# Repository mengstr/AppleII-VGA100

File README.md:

# Apple II VGA Card 100mm PCB

This is a smaller (fits within a 100x100 mm PCB) version of the PCB for the Apple II VGA card. The
original project with the firmware and instructions is located at https://github.com/markadev/AppleII-VGA

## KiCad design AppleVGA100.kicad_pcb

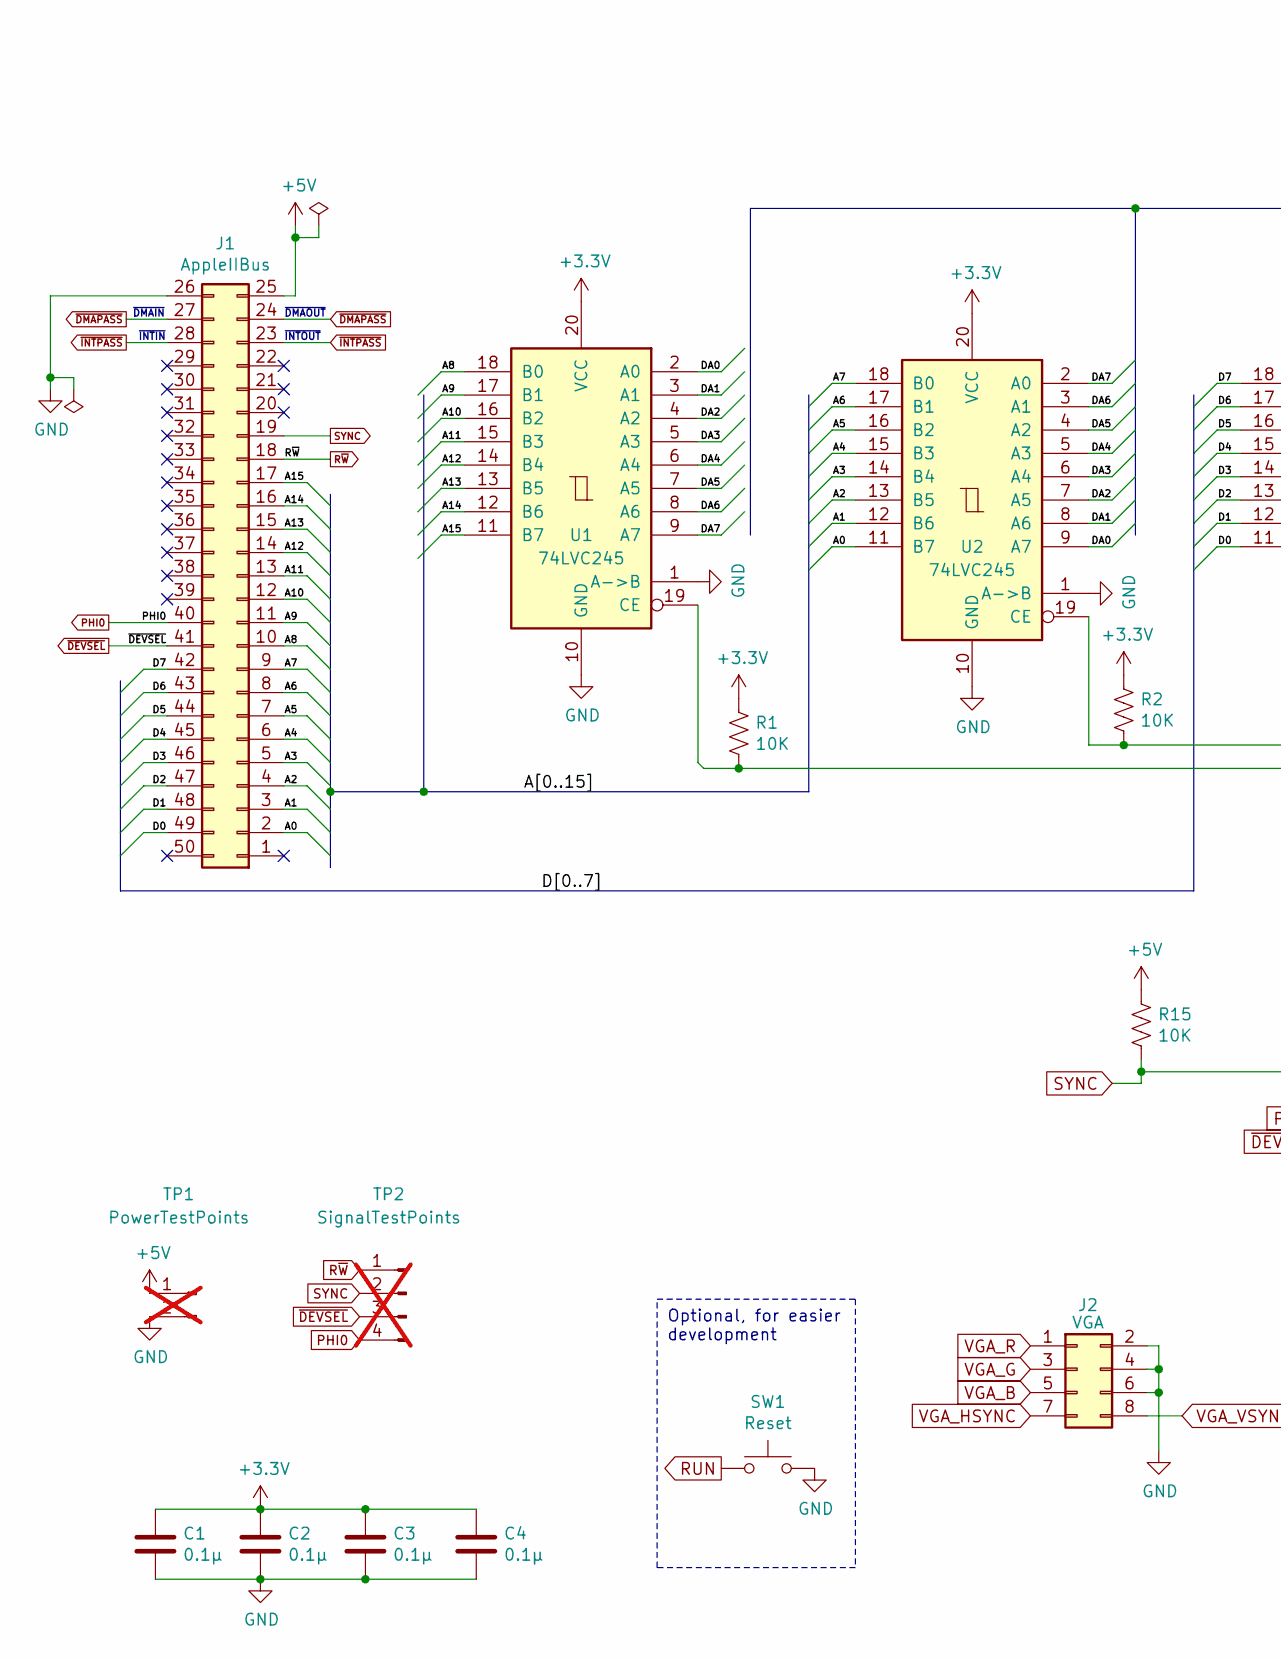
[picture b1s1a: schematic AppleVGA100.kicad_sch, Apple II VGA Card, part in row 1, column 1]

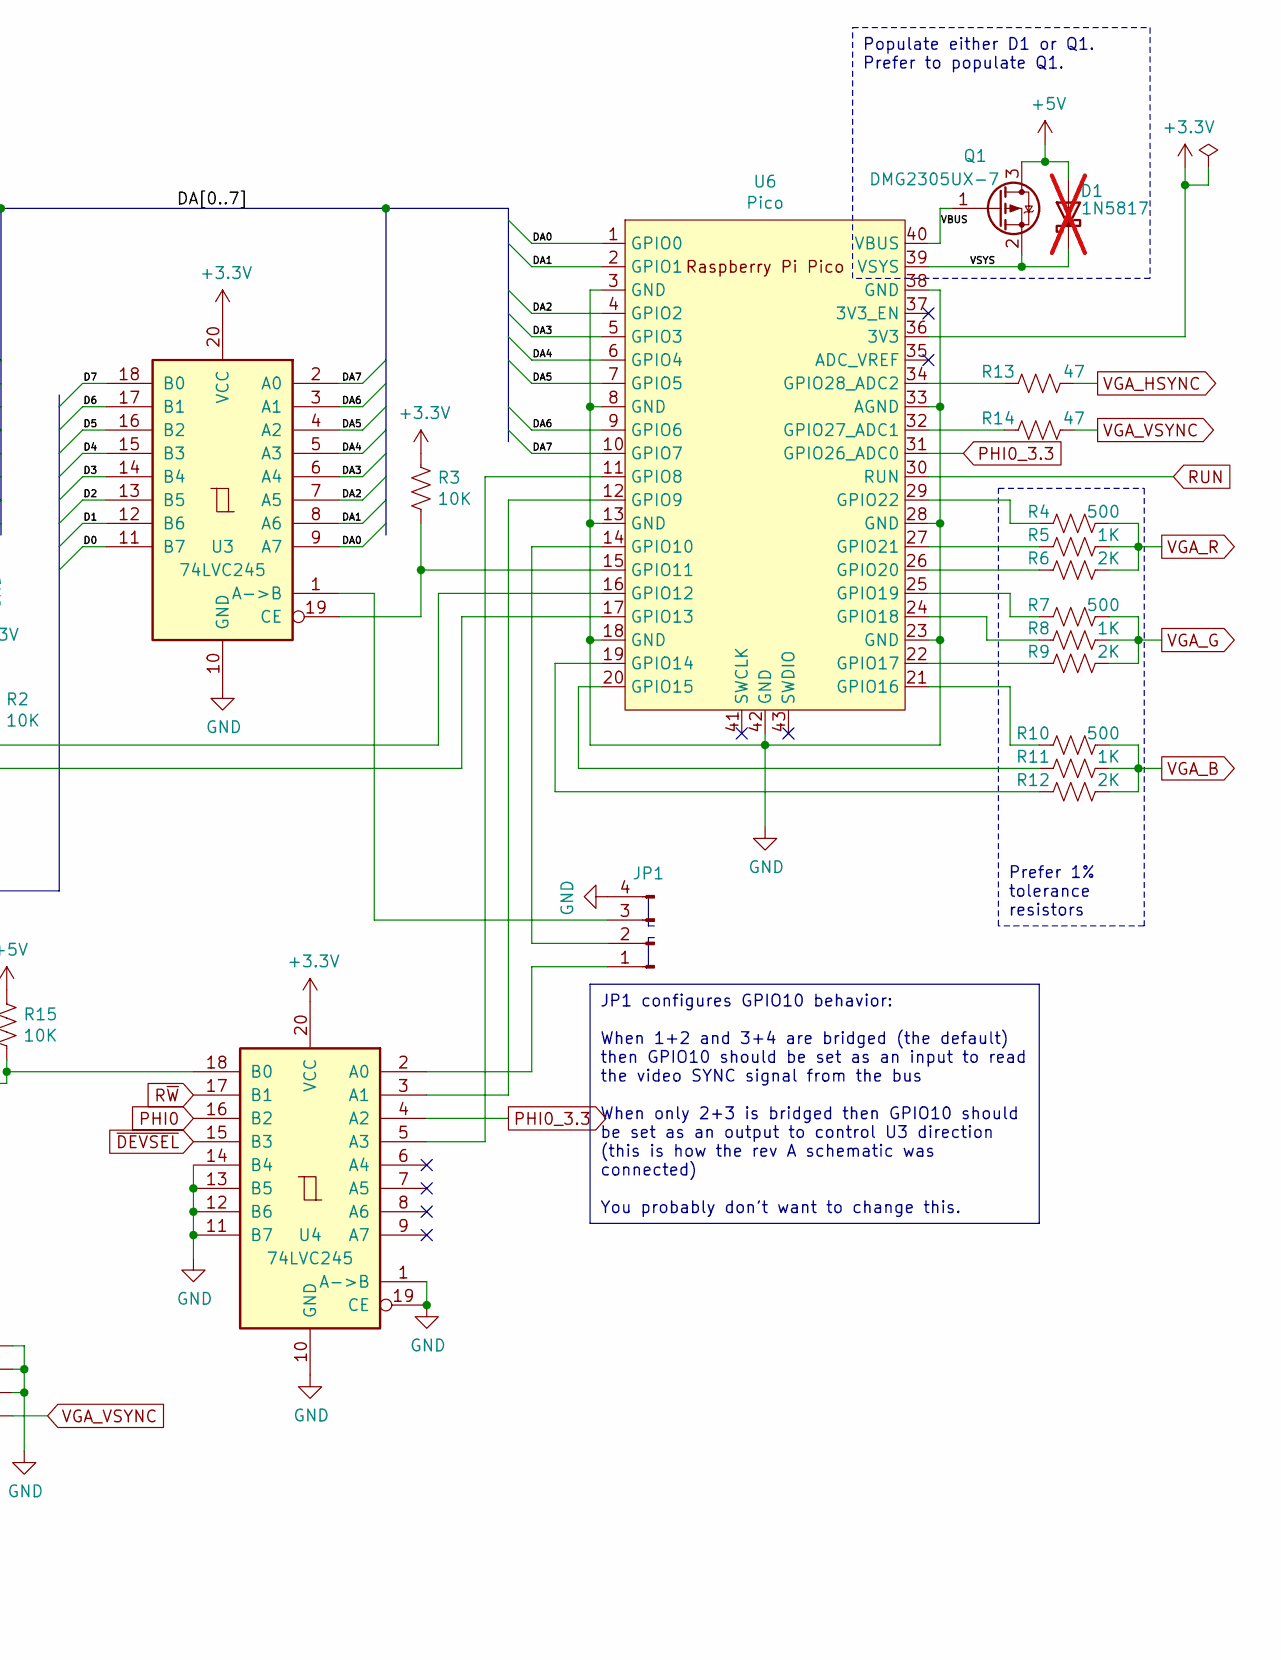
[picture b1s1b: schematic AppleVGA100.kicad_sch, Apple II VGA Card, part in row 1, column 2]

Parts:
C1, C2, C3, C4: 0.1μ; C_Disc_D4.3mm_W1.9mm_P5.00mm; MouserNo 594-A104K15X7RF5TAA
D1: 1N5817; D_DO-41_SOD81_P10.16mm_Horizontal; MouserNo 511-1N5817; not fitted
J1: AppleIIBus; AppleIIBus_Edge
J2: VGA; IDC-Header_2x04_P2.54mm_Vertical; MouserNo 649-75869-232LF
JP1: JumperPads; SolderJumper-4_P1.3mm_Bridged12_34_RoundedPad1.0x1.5mm_Numb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
Q1: DMG2305UX-7; SOT-23; MouserNo 621-DMG2305UX-7
R1, R2, R3, R15: 10K; R_Axial_DIN0207_L6.3mm_D2.5mm_P10.16mm_Thin_Horizontal; MouserNo 603-CFR-25JR-5210K
R4, R7, R10: 500; R_Axial_DIN0207_L6.3mm_D2.5mm_P10.16mm_Thin_Horizontal; MouserNo 603-MFR-25FBF52-499R
R5, R8, R11: 1K; R_Axial_DIN0207_L6.3mm_D2.5mm_P10.16mm_Thin_Horizontal; MouserNo 603-MFR-25FBF52-1K
R6, R9, R12: 2K; R_Axial_DIN0207_L6.3mm_D2.5mm_P10.16mm_Thin_Horizontal; MouserNo 603-MFR-25FBF52-2K
R13, R14: 47; R_Axial_DIN0207_L6.3mm_D2.5mm_P10.16mm_Thin_Horizontal; MouserNo 603-MFR-25FTF52-47R
SW1: Reset; SW_PUSH_6mm_H5mm; MouserNo 506-FSM4JH
TP1: PowerTestPoints; PinHeader_1x02_P2.54mm_Vertical; not fitted
TP2: SignalTestPoints; PinHeader_1x04_P2.54mm_Vertical; not fitted
U1, U2, U3, U4: 74LVC245; DIP-20_W7.62mm_Socket; MouserNo 595-SN74LVC245AN
U6: Pico; RPi_Pico_SMD_TH

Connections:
+3.3V: C1.1, C2.1, C3.1, C4.1, R1.1, R2.1, R3.1, U1.20 (VCC), U2.20 (VCC), U3.20 (VCC), U4.20 (VCC), U6.36 (3V3)
+5V: D1.2 (A), J1.25, Q1.3 (D), R15.1, TP1.1
/A0: J1.2, U2.11 (B7)
/A1: J1.3, U2.12 (B6)
/A2: J1.4, U2.13 (B5)
/A3: J1.5, U2.14 (B4)
/A4: J1.6, U2.15 (B3)
/A5: J1.7, U2.16 (B2)
/A6: J1.8, U2.17 (B1)
/A7: J1.9, U2.18 (B0)
/A8: J1.10, U1.18 (B0)
/A9: J1.11, U1.17 (B1)
/A10: J1.12, U1.16 (B2)
/A11: J1.13, U1.15 (B3)
/A12: J1.14, U1.14 (B4)
/A13: J1.15, U1.13 (B5)
/A14: J1.16, U1.12 (B6)
/A15: J1.17, U1.11 (B7)
/D0: J1.49, U3.11 (B7)
/D1: J1.48, U3.12 (B6)
/D2: J1.47, U3.13 (B5)
/D3: J1.46, U3.14 (B4)
/D4: J1.45, U3.15 (B3)
/D5: J1.44, U3.16 (B2)
/D6: J1.43, U3.17 (B1)
/D7: J1.42, U3.18 (B0)
/DA0: U1.2 (A0), U2.9 (A7), U3.9 (A7), U6.1 (GPIO0)
/DA1: U1.3 (A1), U2.8 (A6), U3.8 (A6), U6.2 (GPIO1)
/DA2: U1.4 (A2), U2.7 (A5), U3.7 (A5), U6.4 (GPIO2)
/DA3: U1.5 (A3), U2.6 (A4), U3.6 (A4), U6.5 (GPIO3)
/DA4: U1.6 (A4), U2.5 (A3), U3.5 (A3), U6.6 (GPIO4)
/DA5: U1.7 (A5), U2.4 (A2), U3.4 (A2), U6.7 (GPIO5)
/DA6: U1.8 (A6), U2.3 (A1), U3.3 (A1), U6.9 (GPIO6)
/DA7: U1.9 (A7), U2.2 (A0), U3.2 (A0), U6.10 (GPIO7)
/VBUS: Q1.1 (G), U6.40 (VBUS)
/VSYS: D1.1 (K), Q1.2 (S), U6.39 (VSYS)
GND: C1.2, C2.2, C3.2, C4.2, J1.26, J2.2, J2.4, J2.6, JP1.4, SW1.2, TP1.2, U1.1 (A->B), U1.10 (GND), U2.1 (A->B), U2.10 (GND), U3.10 (GND), U4.1 (A->B), U4.10 (GND), U4.11 (B7), U4.12 (B6), U4.13 (B5), U4.14 (B4), U4.19 (CE), U6.3 (GND), U6.8 (GND), U6.13 (GND), U6.18 (GND), U6.23 (GND), U6.28 (GND), U6.33 (AGND), U6.38 (GND), U6.42 (GND)
unnamed: JP1.1, U4.2 (A0)
unnamed: JP1.2, U6.14 (GPIO10)
unnamed: JP1.3, U3.1 (A->B)
unnamed: R1.2, U1.19 (CE), U6.17 (GPIO13)
unnamed: R2.2, U2.19 (CE), U6.16 (GPIO12)
unnamed: R3.2, U3.19 (CE), U6.15 (GPIO11)
unnamed: U4.3 (A1), U6.12 (GPIO9)
unnamed: U4.5 (A3), U6.11 (GPIO8)
unnamed: R12.1, U6.19 (GPIO14)
unnamed: R11.1, U6.20 (GPIO15)
unnamed: R10.1, U6.21 (GPIO16)
unnamed: R9.1, U6.22 (GPIO17)
unnamed: R8.1, U6.24 (GPIO18)
unnamed: R7.1, U6.25 (GPIO19)
unnamed: R6.1, U6.26 (GPIO20)
unnamed: R5.1, U6.27 (GPIO21)
unnamed: R4.1, U6.29 (GPIO22)
unnamed: R14.1, U6.32 (GPIO27_ADC1)
unnamed: R13.1, U6.34 (GPIO28_ADC2)
PHI0: J1.40, TP2.4, U4.16 (B2)
PHI0_3.3: U4.4 (A2), U6.31 (GPIO26_ADC0)
RUN: SW1.1, U6.30 (RUN)
R~W: J1.18, TP2.1, U4.17 (B1)
SYNC: J1.19, R15.2, TP2.2, U4.18 (B0)
VGA_B: J2.5, R10.2, R11.2, R12.2
VGA_G: J2.3, R7.2, R8.2, R9.2
VGA_HSYNC: J2.7, R13.2
VGA_R: J2.1, R4.2, R5.2, R6.2
VGA_VSYNC: J2.8, R14.2
~DEVSEL: J1.41, TP2.3, U4.15 (B3)
~DMAPASS: J1.24, J1.27
~INTPASS: J1.23, J1.28

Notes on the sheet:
Optional, for easier development
Populate either D1 or Q1. Prefer to populate Q1.
JP1 configures GPIO10 behavior: When 1+2 and 3+4 are bridged (the default) then GPIO10 should be set as an input to read the video SYNC signal from the bus When only 2+3 is bridged then GPIO10 should be set as an output to control U3 direction (this is how the rev A schematic was connected) You pro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
Prefer 1% tolerance resistors
~{DMAIN}
~{INTOUT}
~{DMAOUT}
~{INTIN}

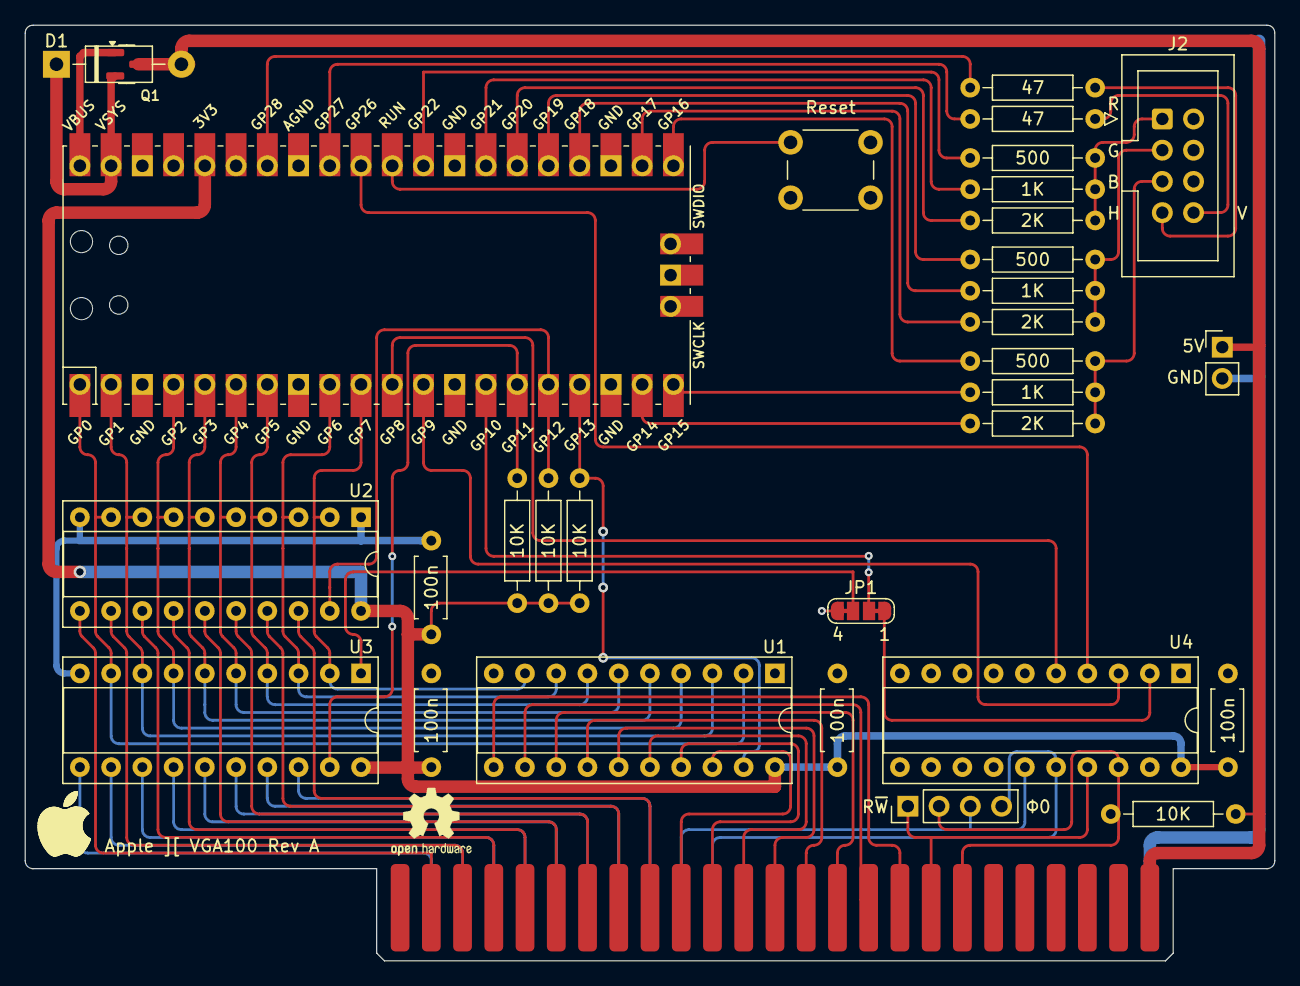
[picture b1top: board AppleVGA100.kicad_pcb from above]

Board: 2 copper layers, 101.6 x 76.1 mm, 33 parts (0 on the bottom side), 69 nets.

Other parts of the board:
LOGO1: AppleLogo_5mm

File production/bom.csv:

Designator,Footprint,Quantity,Value,LCSC Part #
"C1, C2, C3, C4",C_Disc_D4.7mm_W2.5mm_P7.62mm,4,0.1μ,
D1,D_DO-41_SOD81_P10.16mm_Horizontal,1,1N5817,
J2,IDC-Header_2x04_P2.54mm_Vertical,1,VGA,
Q1,SOT-23,1,DMG2305UX-7,
"R1, R15, R2, R3",R_Axial_DIN0207_L6.3mm_D2.5mm_P10.16mm_Thin_Horizontal,4,10K,
"R10, R4, R7",R_Axial_DIN0207_L6.3mm_D2.5mm_P10.16mm_Thin_Horizontal,3,500,
"R11, R5, R8",R_Axial_DIN0207_L6.3mm_D2.5mm_P10.16mm_Thin_Horizontal,3,1K,
"R12, R6, R9",R_Axial_DIN0207_L6.3mm_D2.5mm_P10.16mm_Thin_Horizontal,3,2K,
"R13, R14",R_Axial_DIN0207_L6.3mm_D2.5mm_P10.16mm_Thin_Horizontal,2,47,
SW1,SW_PUSH_6mm_H5mm,1,Reset,
"U1, U2, U3, U4",DIP-20_W7.62mm_Socket,4,74LVC245,
U6,RPi_Pico_SMD_TH,1,Pico,

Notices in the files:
AppleVGA100.kicad_pcb:
Licensed under CERN-OHL-P V2.0 (https://ohwr.org/cern_ohl_p_v2.txt)
Copyright (c) 2021-2023 Mark Aikens
